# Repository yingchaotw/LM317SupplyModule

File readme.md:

# LM317 Supply Module

Although I have a high-power power supply, it only provides a single channel of voltage. Since I require multiple voltage levels, I have decided to design an LDO supply module to regulate the voltage accordingly.
I envision the supply module to be assembled in a manner similar to Lego blocks, allowing for easy expansion and modification.

## Circuit

## PCB 2D View
Single layer PCB

## PCB 3D View

### Bill Of Material

| Ref         | Qnty | Value                  | Cmp name               | Footprint                                                                   | Description                                                                                              | Vendor | DNP |
|-------------|------|------------------------|------------------------|-----------------------------------------------------------------------------|----------------------------------------------------------------------------------------------------------|--------|-----|
| C1          | 1    | 10nF/16V               | C_Small                | Capacitor_SMD:C_0603_1608Metric                                             | Unpolarized capacitor, small symbol                                                                      |        |     |
| C2          | 1    | 100u/25V               | C_Polarized_Small_US   | Capacitor_Tantalum_SMD:CP_EIA-7343-30_AVX-N                                 | Polarized capacitor, small US symbol                                                                     |        |     |
| C3          | 1    | 100nF/16V              | C_Small                | Capacitor_SMD:C_0603_1608Metric                                             | Unpolarized capacitor, small symbol                                                                      |        |     |
| C4          | 1    | 100u/25V               | C_Polarized_Small_US   | Capacitor_SMD:C_0603_1608Metric                                             | Polarized capacitor, small US symbol                                                                     |        |     |
| D1, D2      | 2    | KDZVTF16B              | D_Small                | Diode_SMD:D_SOD-123F                                                        | Diode, small symbol                                                                                      |        |     |
| D3, D4      | 2    | 1N4007                 | D_Small                | Diode_SMD:D_SMA                                                             | Diode, small symbol                                                                                      |        |     |
| D5          | 1    | LED_Green              | LED_Small              | LED_SMD:LED_1206_3216Metric                                                 | Light emitting diode, small symbol                                                                       |        |     |
| J1          | 1    | Conn_01x02             | Conn_01x02             | Connector_Phoenix_MC:PhoenixContact_MC_1,5_2-G-3.81_1x02_P3.81mm_Horizontal | Generic connector, single row, 01x02, script generated   (kicad-library-utils/schlib/autogen/connector/) |        |     |
| J2, J3      | 2    | Conn_01x02             | Conn_01x02             | Connector_Molex:Molex_KK-254_AE-6410-02A_1x02_P2.54mm_Vertical              | Generic connector, single row, 01x02, script generated   (kicad-library-utils/schlib/autogen/connector/) |        |     |
| JP1, JP2    | 2    | SolderJumper_2_Open    | SolderJumper_2_Open    | Jumper:SolderJumper-2_P1.3mm_Open_TrianglePad1.0x1.5mm                      | Solder Jumper, 2-pole, open                                                                              |        |     |
| JP3         | 1    | SolderJumper_2_Bridged | SolderJumper_2_Bridged | Jumper:SolderJumper-2_P1.3mm_Bridged_RoundedPad1.0x1.5mm                    | Solder Jumper, 2-pole, closed/bridged                                                                    |        |     |
| Q1          | 1    | [DMP4011SPSQ](https://www.diodes.com/part/view/DMP4011SPSQ/#tab-details)           | DMP3013SFV             | Supply-Module-Library:Diodes_PowerDI5060-8                                  | -12A Id, -30V Vds, P-Channel Power MOSFET, 9.5mOhm Ron, 33.7nC Qg (typ),   PowerDI3333-8                 |        |     |
| Q2          | 1    | 2N7002                 | NMOS                   | Package_TO_SOT_SMD:SOT-23                                                   | N-MOSFET transistor, drain/source/gate                                                                   |        |     |
| R1          | 1    | 100R/5%                | R_Small_US             | Resistor_SMD:R_0603_1608Metric                                              | Resistor, small US symbol                                                                                |        |     |
| R2          | 1    | 10K/5%                 | R_Small_US             | Resistor_SMD:R_0603_1608Metric                                              | Resistor, small US symbol                                                                                |        |     |
| R3, R4, R9  | 3    | 100K/5%                | R_Small_US             | Resistor_SMD:R_0603_1608Metric                                              | Resistor, small US symbol                                                                                |        |     |
| R5, R8, R10 | 3    | 1K/5%                  | R_Small_US             | Resistor_SMD:R_0603_1608Metric                                              | Resistor, small US symbol                                                                                |        |     |
| R6          | 1    | 1M/5%                  | R_Small_US             | Resistor_SMD:R_0603_1608Metric                                              | Resistor, small US symbol                                                                                |        |     |
| R7          | 1    | 120R/5%                | R_Small_US             | Resistor_SMD:R_0603_1608Metric                                              | Resistor, small US symbol                                                                                |        |     |
| RV1         | 1    | 10K                    | R_Potentiometer_Small  | Supply-Module-Library:Variable_Resistance_PV36W                             | Potentiometer                                                                                            |        |     |
| SW1         | 1    | SW_SPDT                | SW_SPDT | Supply-Module-Library:SW_DIP_5176_SPDT                                      | Switch, single pole double throw                                                                         |    [5176A](https://kinsten.com.tw/index.php?route=product/product&product_id=49621&search=壓動開關5.8×5.8mm) / [TL2203EE](https://mou.sr/3LJwoE3)    |     |
| U1          | 1    | LM317_SOT-223          | [LM317_SOT-223](https://www.ti.com/product/LM317)         | Package_TO_SOT_SMD:SOT-223-3_TabPin2                                        | 1.5A 35V Adjustable Linear Regulator, SOT-223                                                            |        |     |

## Toolchain

Use Open-Source free software to designed this project.

### KiCAD

KiCad (/ˈkiːˌkæd/ KEE-kad) is a free software suite for electronic design automation (EDA). It facilitates the design and simulation of electronic hardware. It features an integrated environment for schematic capture, PCB layout, manufacturing file viewing, ngspice-provided SPICE simulation, and engineering calculation. Tools exist within the package to create bill of materials, artwork, Gerber files, and 3D models of the PCB and its components. -- [Refer to Wiki](https://en.wikipedia.org/wiki/KiCad)

#### kicad V7.0.2 issue
When I run electrical rules checker, KiCAD show me [ERC report](./Circuit%20-%20LM317%20Supply%20Module/ERC-issue.rpt). This issue refer to [Error reading simulation model from symbol](https://gitlab.com/kicad/code/kicad/-/issues/14569).
about this issue [From 7.0.1 to 7.0.2-0: Error reading simulation model](https://forum.kicad.info/t/from-7-0-1-to-7-0-2-0-error-reading-simulation-model/41837). **It’s a bug in 7.0.2 that will be fixed in 7.0.3.**

### FreeCAD
[&color=FC1107&logo=freecad)](https://www.freecad.org/)

FreeCAD is a general-purpose parametric 3D computer-aided design (CAD) modeler and a building information modeling (BIM) software application with finite element method (FEM) support. It is intended for mechanical engineering product design but also expands to a wider range of uses around engineering, such as architecture or electrical engineering. FreeCAD is free and open-source, under the LGPL-2.0-or-later license, and available for Linux, macOS, and Windows operating systems. Users can extend the functionality of the software using the Python programming language.  -- [Refer to Wiki](https://en.wikipedia.org/wiki/FreeCAD)

# License & Disclaimer

If you have other ideas or suggestions, please feel free to submit an issue.

<br />This work is licensed under a <a rel="license" href="https://creativecommons.org/licenses/by-sa/4.0/">Creative Commons Attribution-ShareAlike 4.0 International License</a>.

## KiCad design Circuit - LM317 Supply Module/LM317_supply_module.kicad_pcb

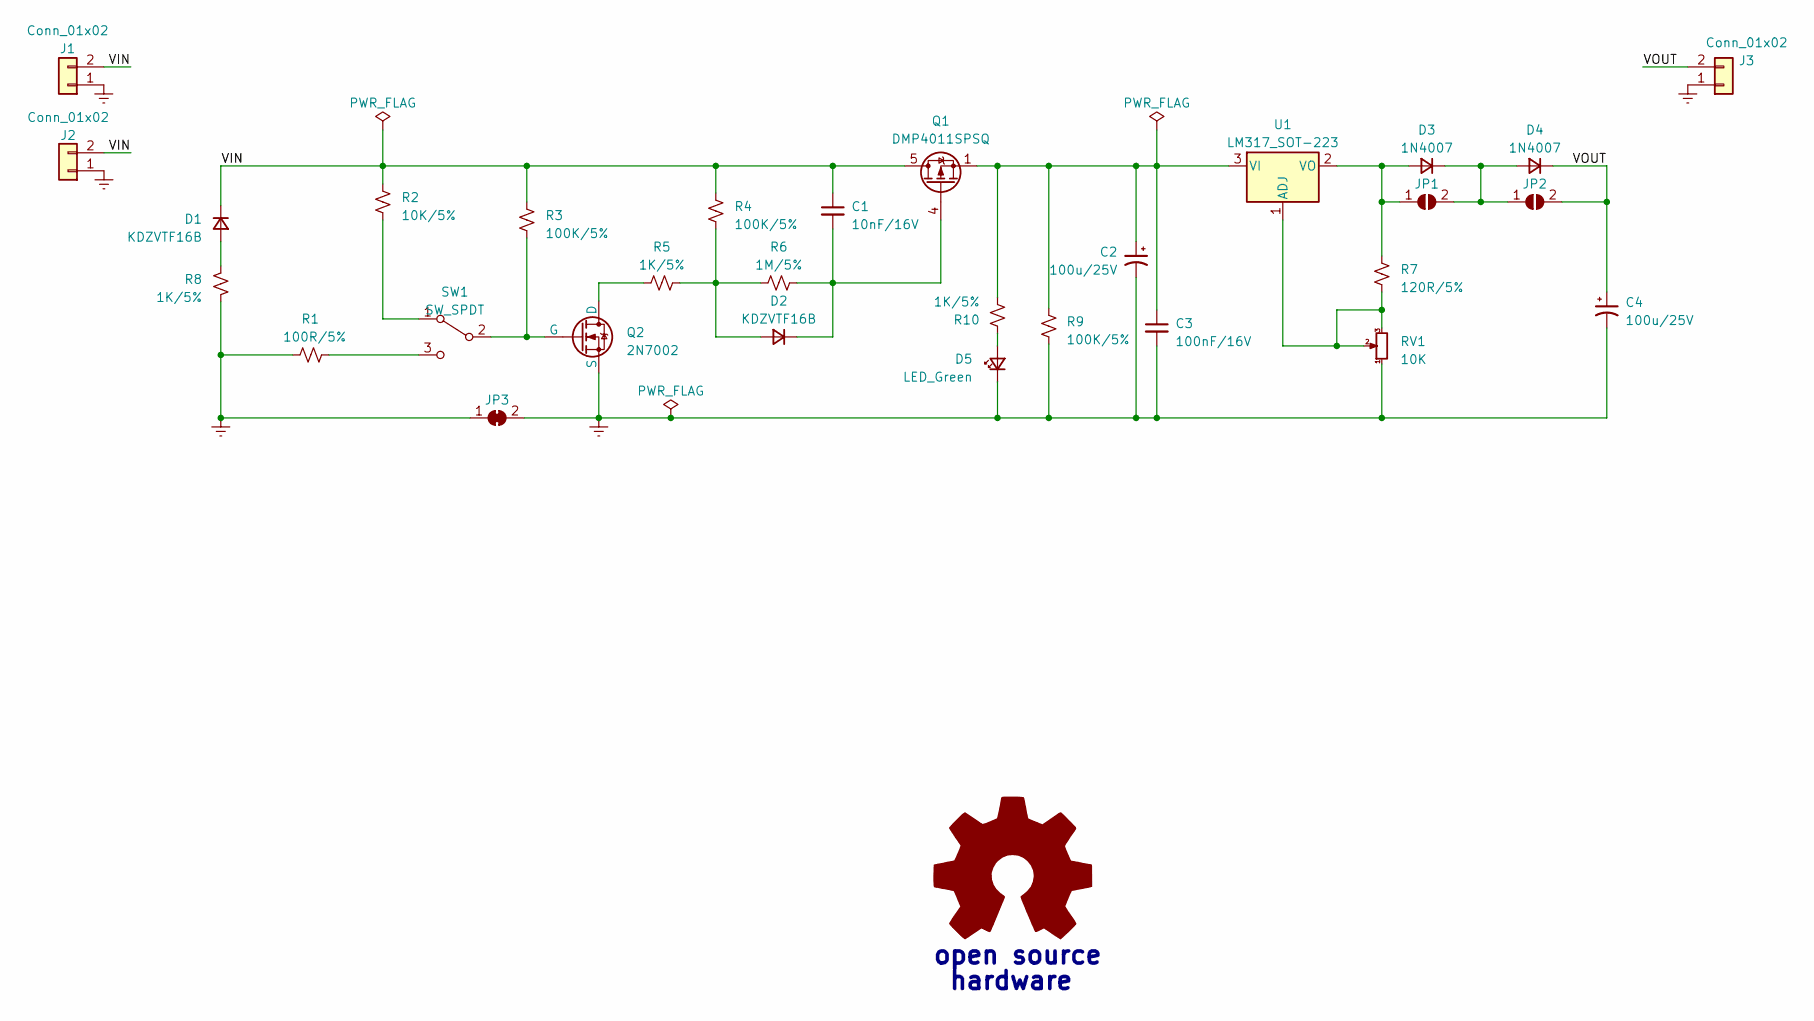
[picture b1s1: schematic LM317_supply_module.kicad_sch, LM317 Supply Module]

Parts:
C1: 10nF/16V; C_0603_1608Metric
C2: 100u/25V; CP_EIA-7343-30_AVX-N
C3: 100nF/16V; C_0603_1608Metric
C4: 100u/25V; C_0603_1608Metric
D1, D2: KDZVTF16B; D_SOD-123F
D3, D4: 1N4007; D_SMA
D5: LED_Green; LED_1206_3216Metric
J1: Conn_01x02; PhoenixContact_MC_1,5_2-G-3.81_1x02_P3.81mm_Horizontal
J2, J3: Conn_01x02; Molex_KK-254_AE-6410-02A_1x02_P2.54mm_Vertical
JP1, JP2: SolderJumper_2_Open; SolderJumper-2_P1.3mm_Open_TrianglePad1.0x1.5mm
JP3: SolderJumper_2_Bridged; SolderJumper-2_P1.3mm_Bridged_RoundedPad1.0x1.5mm
Q1: DMP4011SPSQ; Diodes_PowerDI5060-8
Q2: 2N7002; SOT-23
R1: 100R/5%; R_0603_1608Metric
R2: 10K/5%; R_0603_1608Metric
R3, R4, R9: 100K/5%; R_0603_1608Metric
R5, R8, R10: 1K/5%; R_0603_1608Metric
R6: 1M/5%; R_0603_1608Metric
R7: 120R/5%; R_0603_1608Metric
RV1: 10K; Variable_Resistance_PV36W
SW1: SW_SPDT; SW_DIP_5176_SPDT
U1: LM317_SOT-223; SOT-223-3_TabPin2

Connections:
/VIN: C1.1, D1.1 (K), J1.2, J2.2, Q1.5 (D), R2.1, R3.1, R4.1
/VOUT: C4.1, D4.1 (K), J3.2, JP2.2 (B)
Earth: J1.1, J2.1, JP3.1 (A), R1.1, R8.1
GNDREF: C2.2, C3.2, C4.2, D5.1 (K), J3.1, JP3.2 (B), Q2.3 (S), R9.2, RV1.1
unnamed: D1.2 (A), R8.2
unnamed: D2.2 (A), R4.2, R5.2, R6.1
unnamed: C1.2, D2.1 (K), Q1.4 (G), R6.2
unnamed: D3.2 (A), JP1.1 (A), R7.2, U1.2 (VO)
unnamed: D3.1 (K), D4.2 (A), JP1.2 (B), JP2.1 (A)
unnamed: D5.2 (A), R10.1
unnamed: Q2.1 (D), R5.1
unnamed: Q2.2 (G), R3.2, SW1.2 (B)
unnamed: R2.2, SW1.1 (A)
unnamed: R1.2, SW1.3 (C)
unnamed: R7.1, RV1.2, RV1.3, U1.1 (ADJ)
unnamed: C2.1, C3.1, Q1.1 (S), Q1.2 (S), Q1.3 (S), R9.1, R10.2, U1.3 (VI)

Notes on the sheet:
hardware
open source

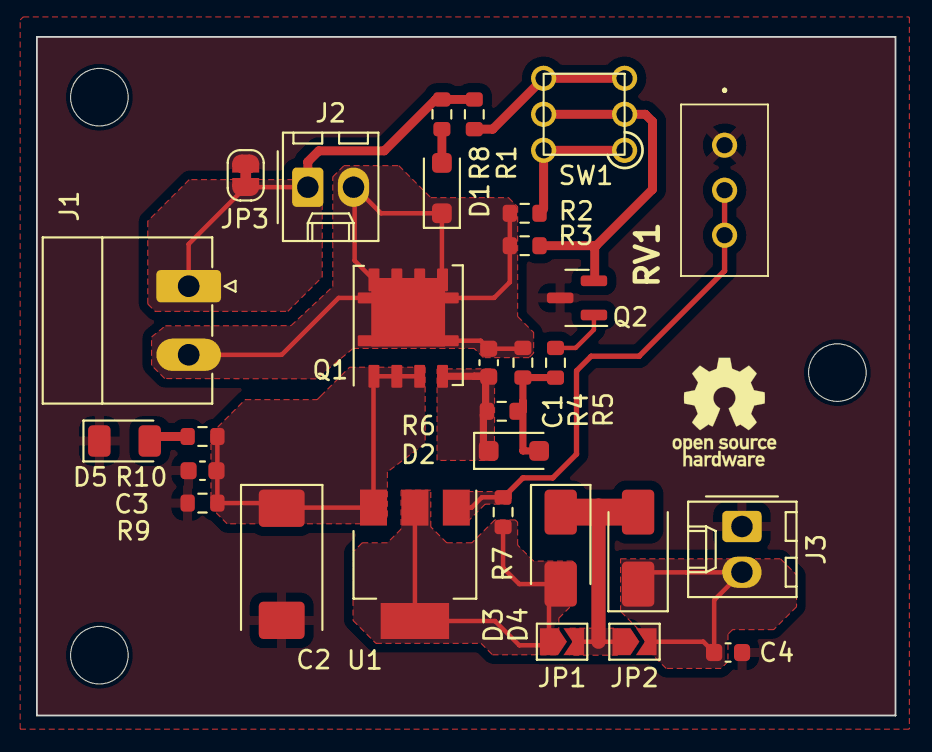
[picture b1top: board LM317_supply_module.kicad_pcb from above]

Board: 2 copper layers, 47.7 x 37.7 mm, 30 parts (0 on the bottom side), 16 nets.

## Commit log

2023-05-04 create PMOS footprint
    update readme.md file
2023-05-05 update all component footprint
    add license CC BY-SA file, update readme
2023-05-07 update PCB Layout
    update schematic power LED, PCB 3D module file, etc..
2023-05-08 PCB Layout Done, DRC OK
    update PCB layout, <NEED> Review Gerber file
2023-05-10 Modify Single Layer PCB
    modify input/output connector & LED size
2023-05-12 Create FUNDING.yml
    Please Donate to me
2023-05-12 Update FUNDING.yml
    modify donate link, add ko_fi & paypal.me/tw1chao

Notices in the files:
Circuit - LM317 Supply Module/LM317_supply_module.kicad_sch:
CC BY-SA 4.0
readme.md:
license - CC BY-SA 4.0
